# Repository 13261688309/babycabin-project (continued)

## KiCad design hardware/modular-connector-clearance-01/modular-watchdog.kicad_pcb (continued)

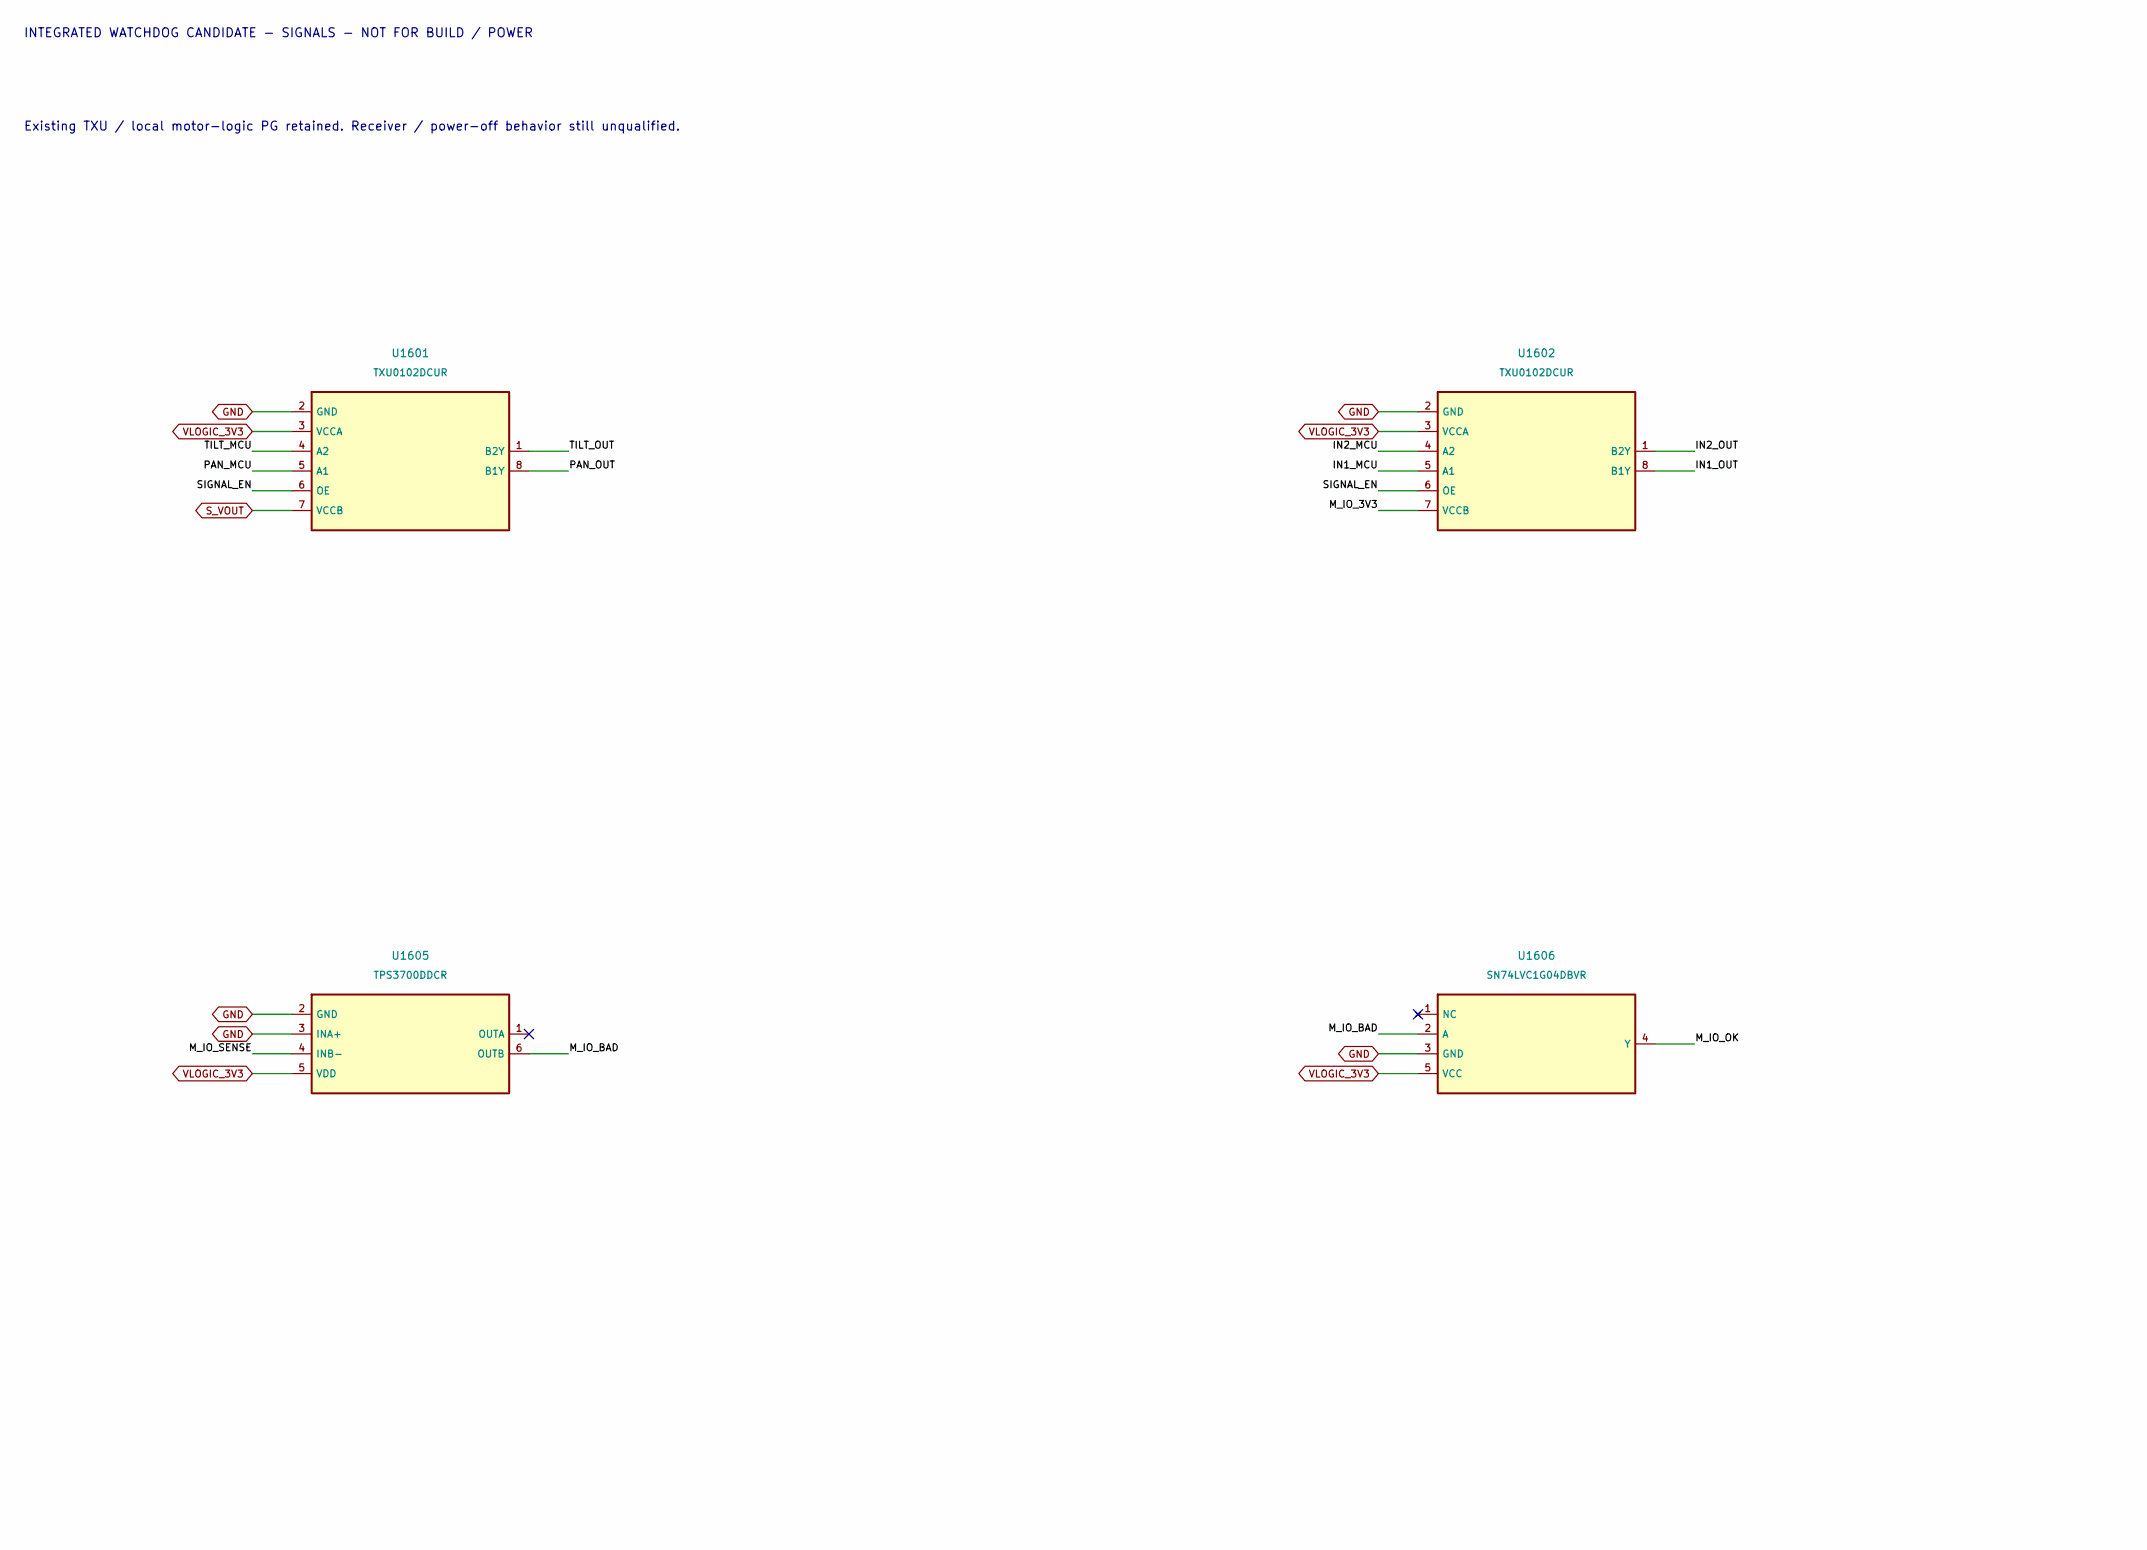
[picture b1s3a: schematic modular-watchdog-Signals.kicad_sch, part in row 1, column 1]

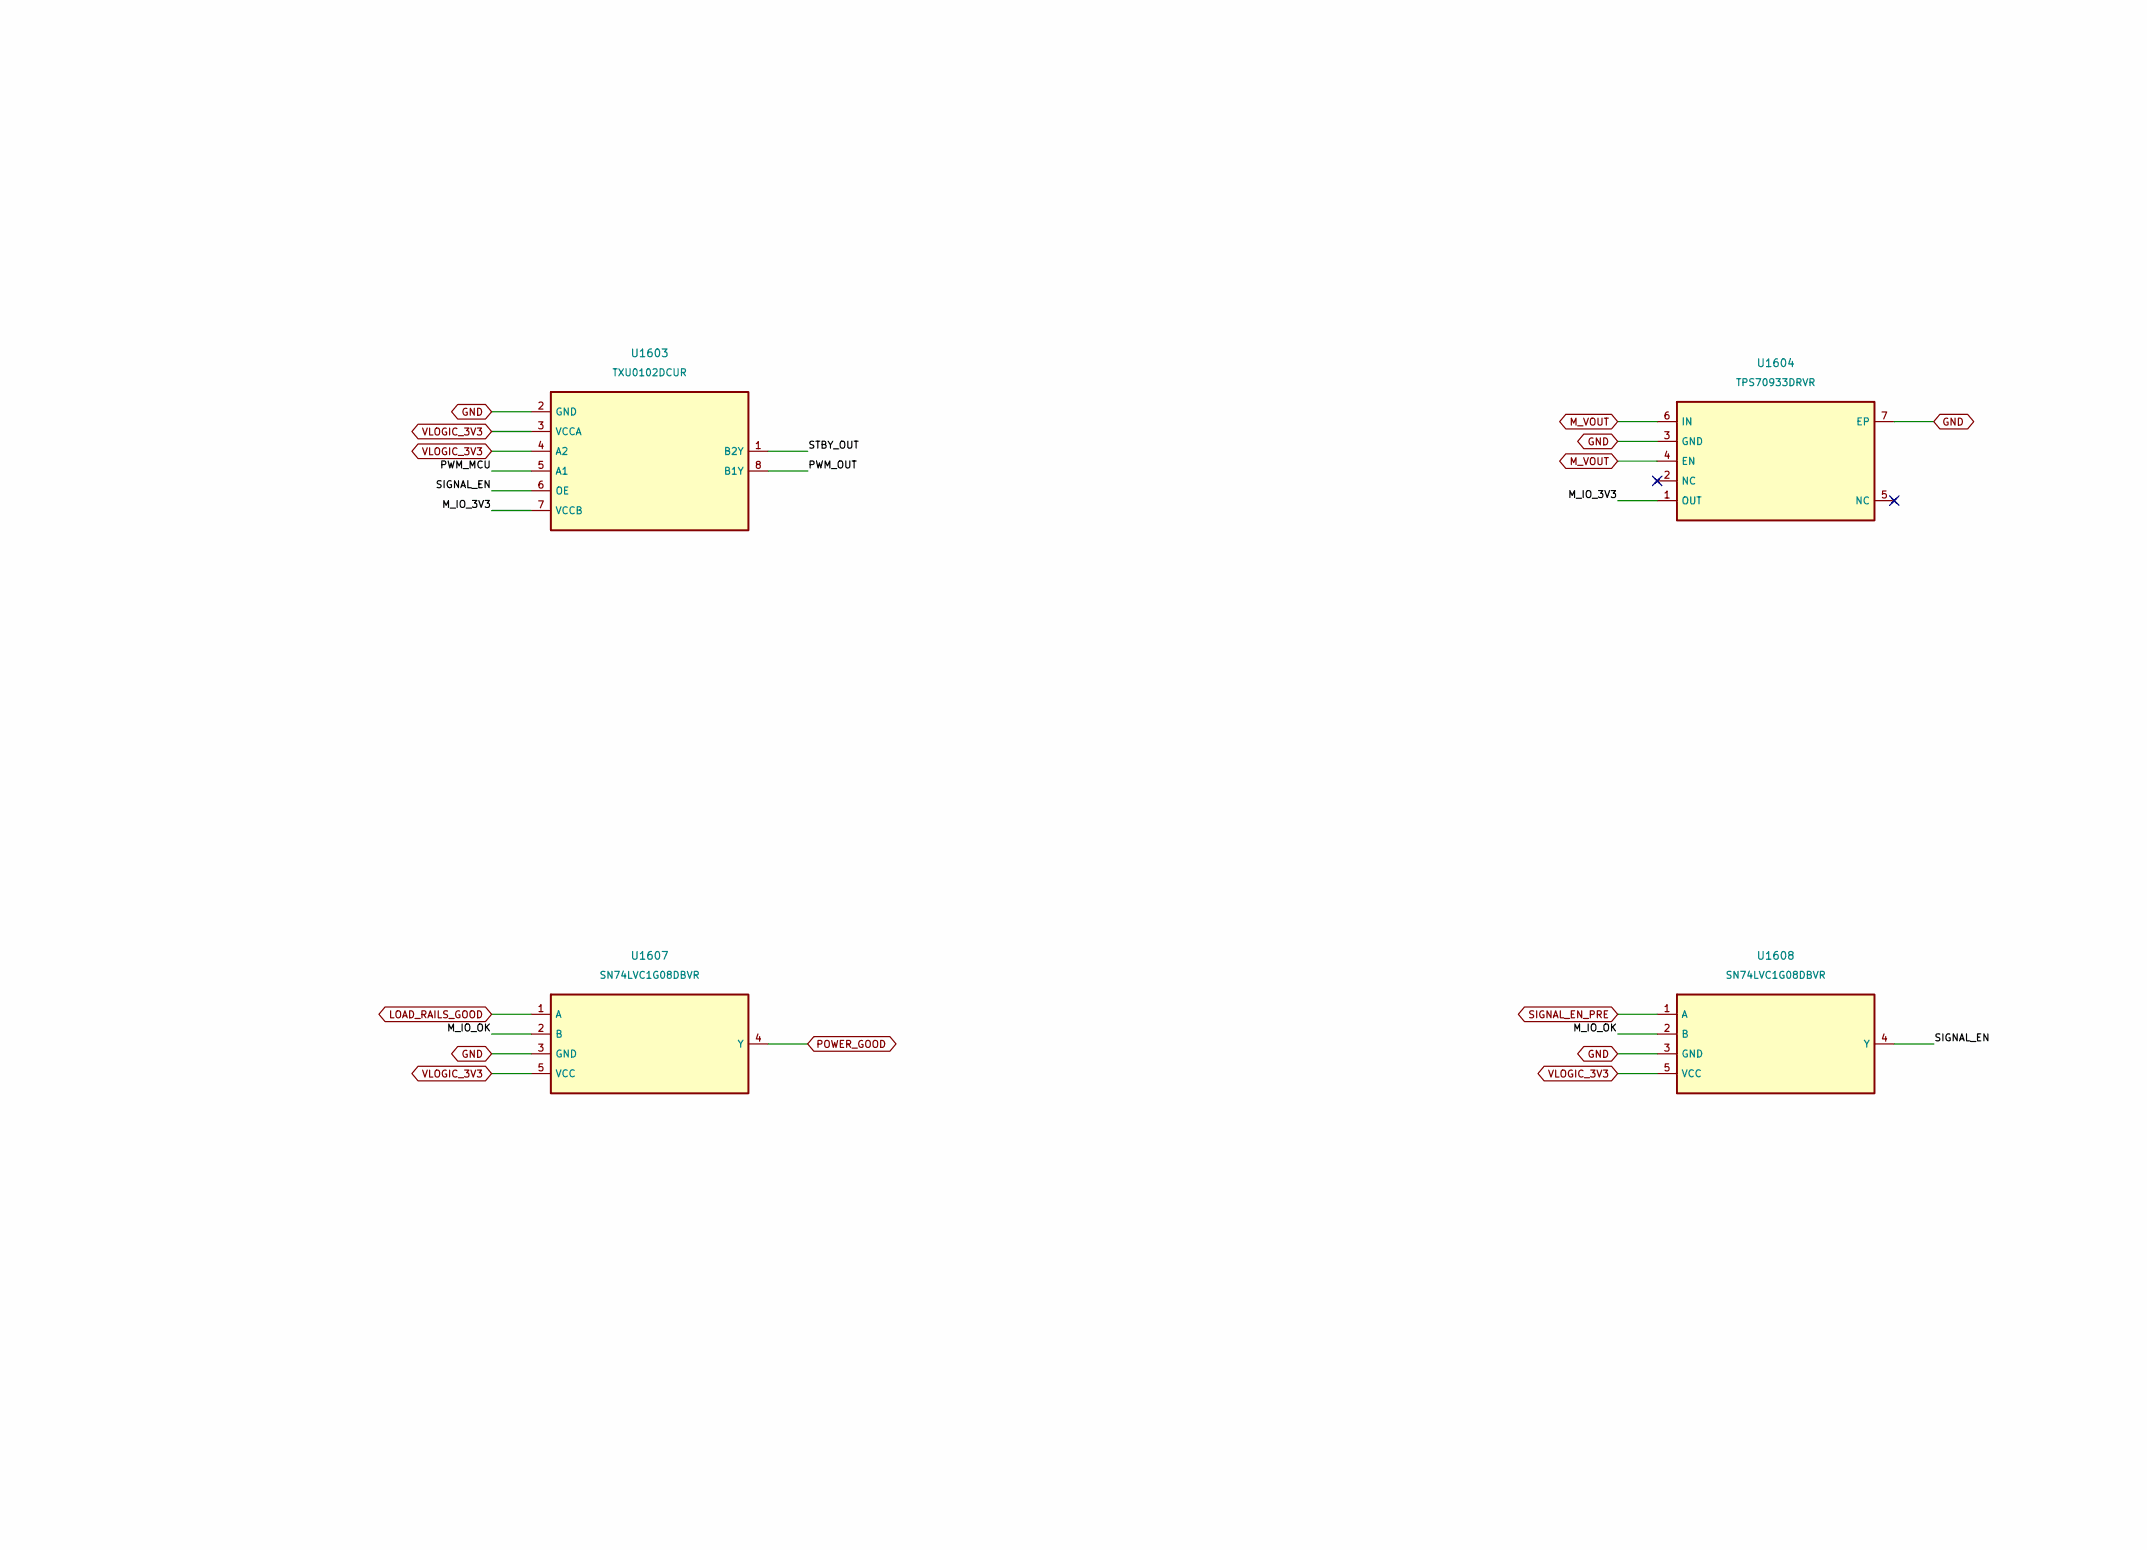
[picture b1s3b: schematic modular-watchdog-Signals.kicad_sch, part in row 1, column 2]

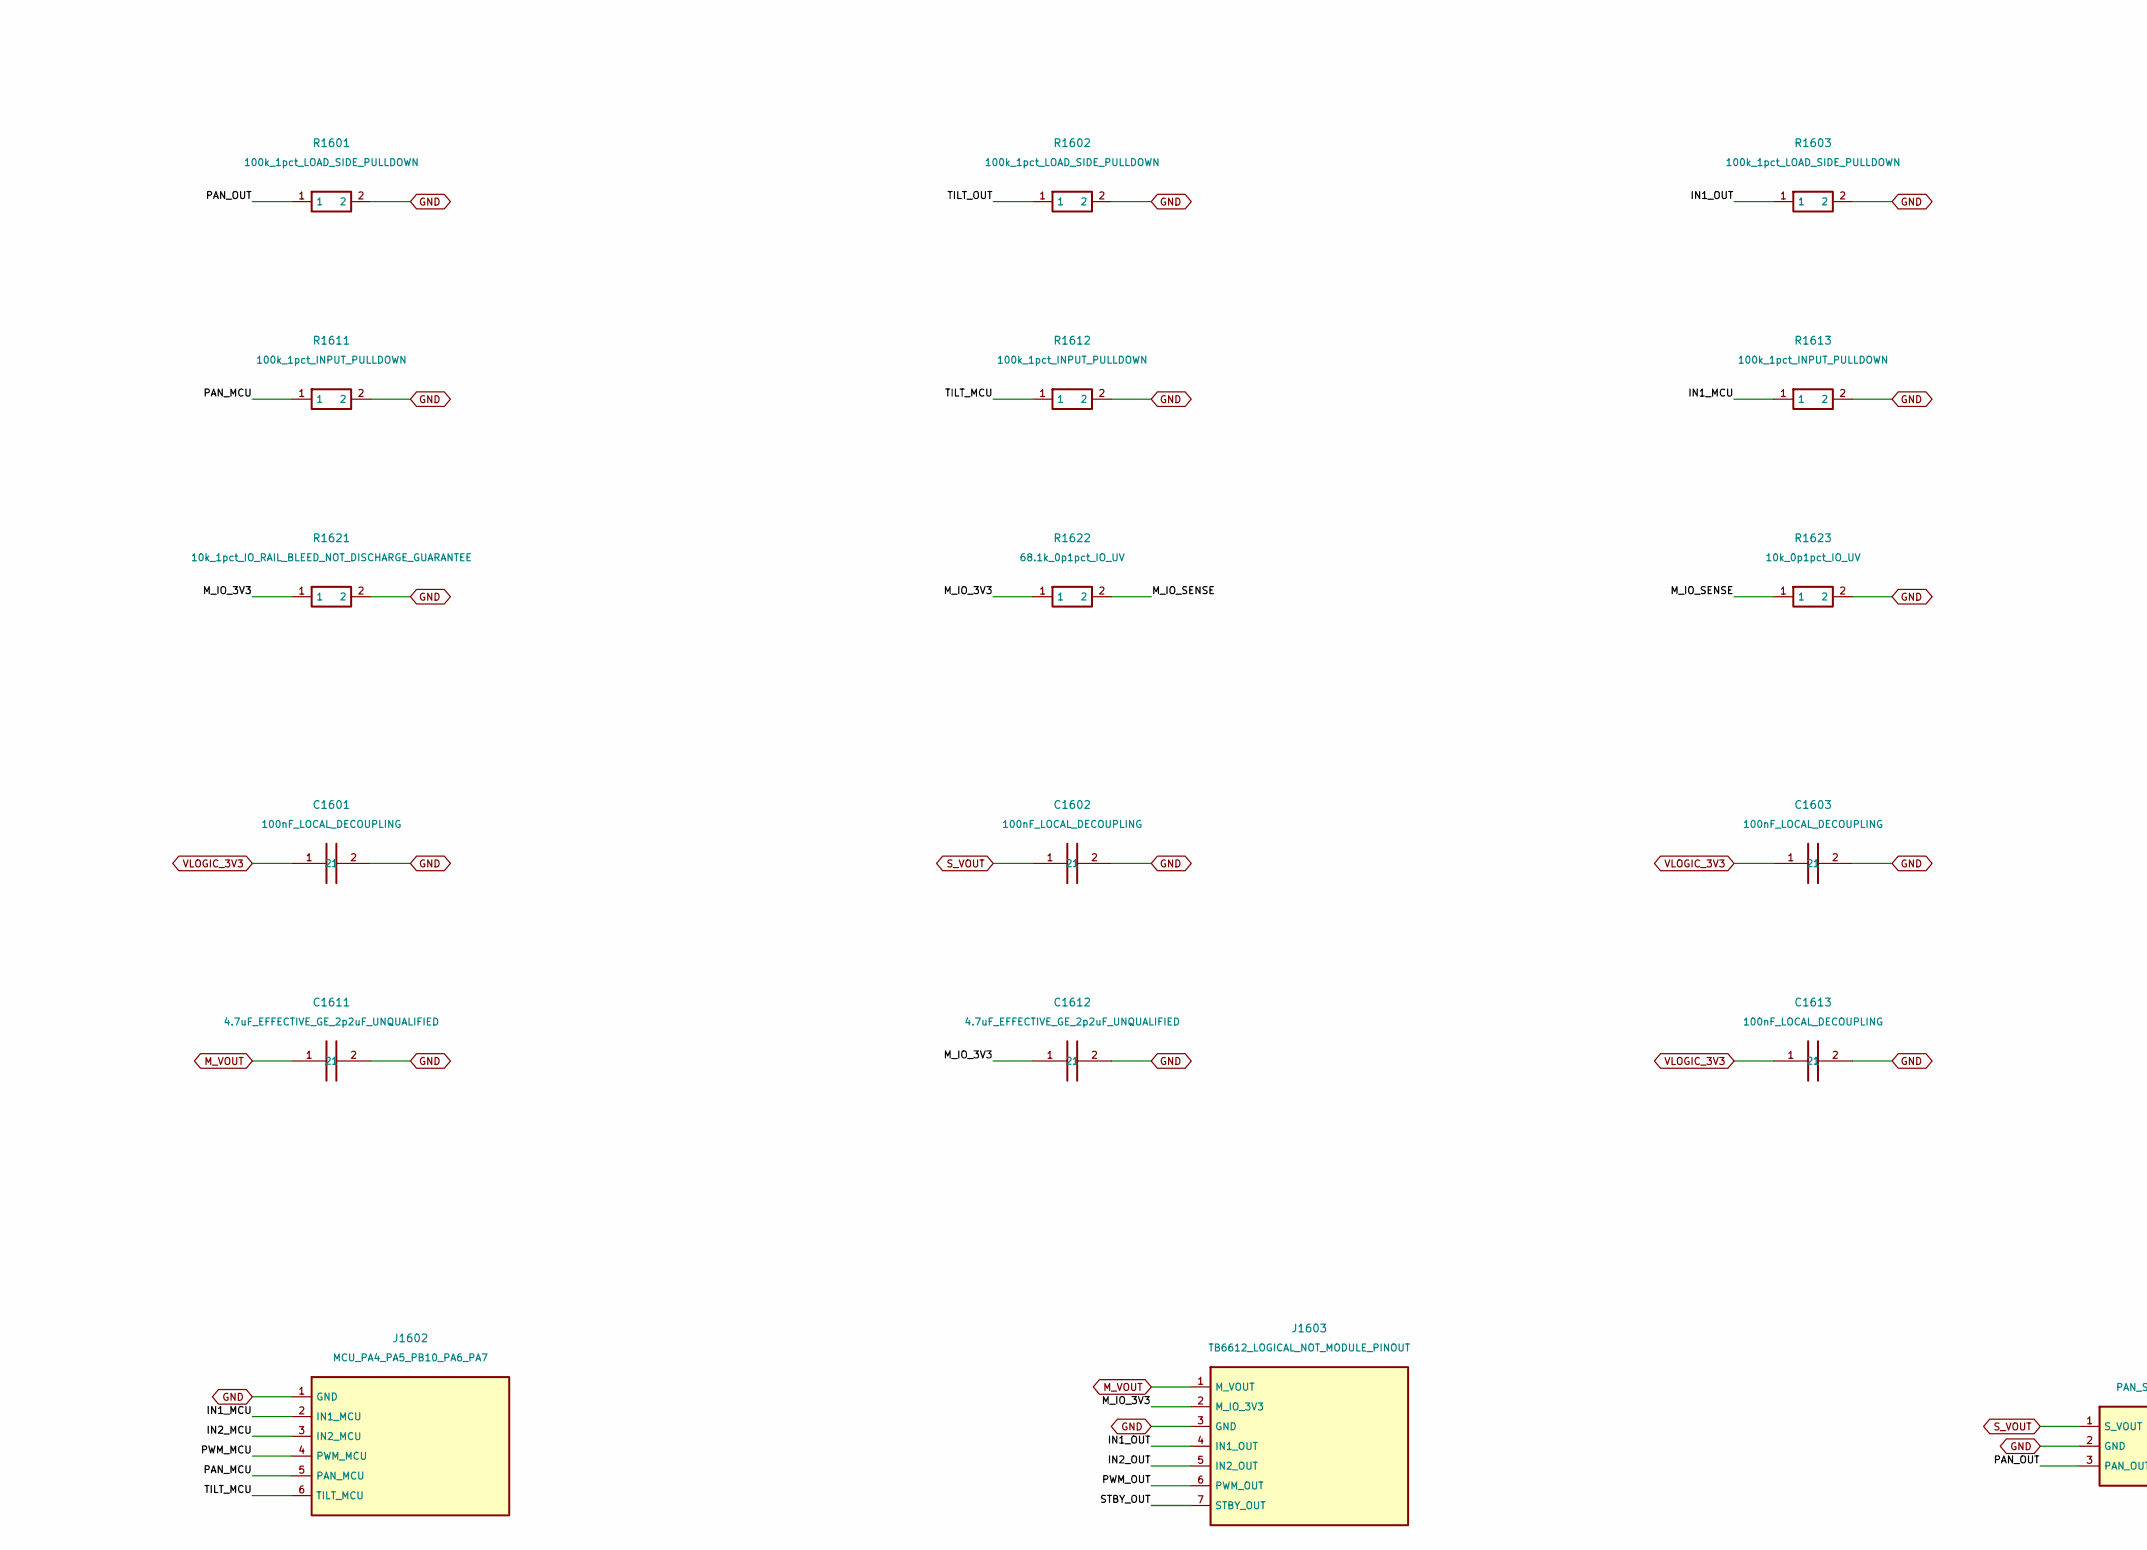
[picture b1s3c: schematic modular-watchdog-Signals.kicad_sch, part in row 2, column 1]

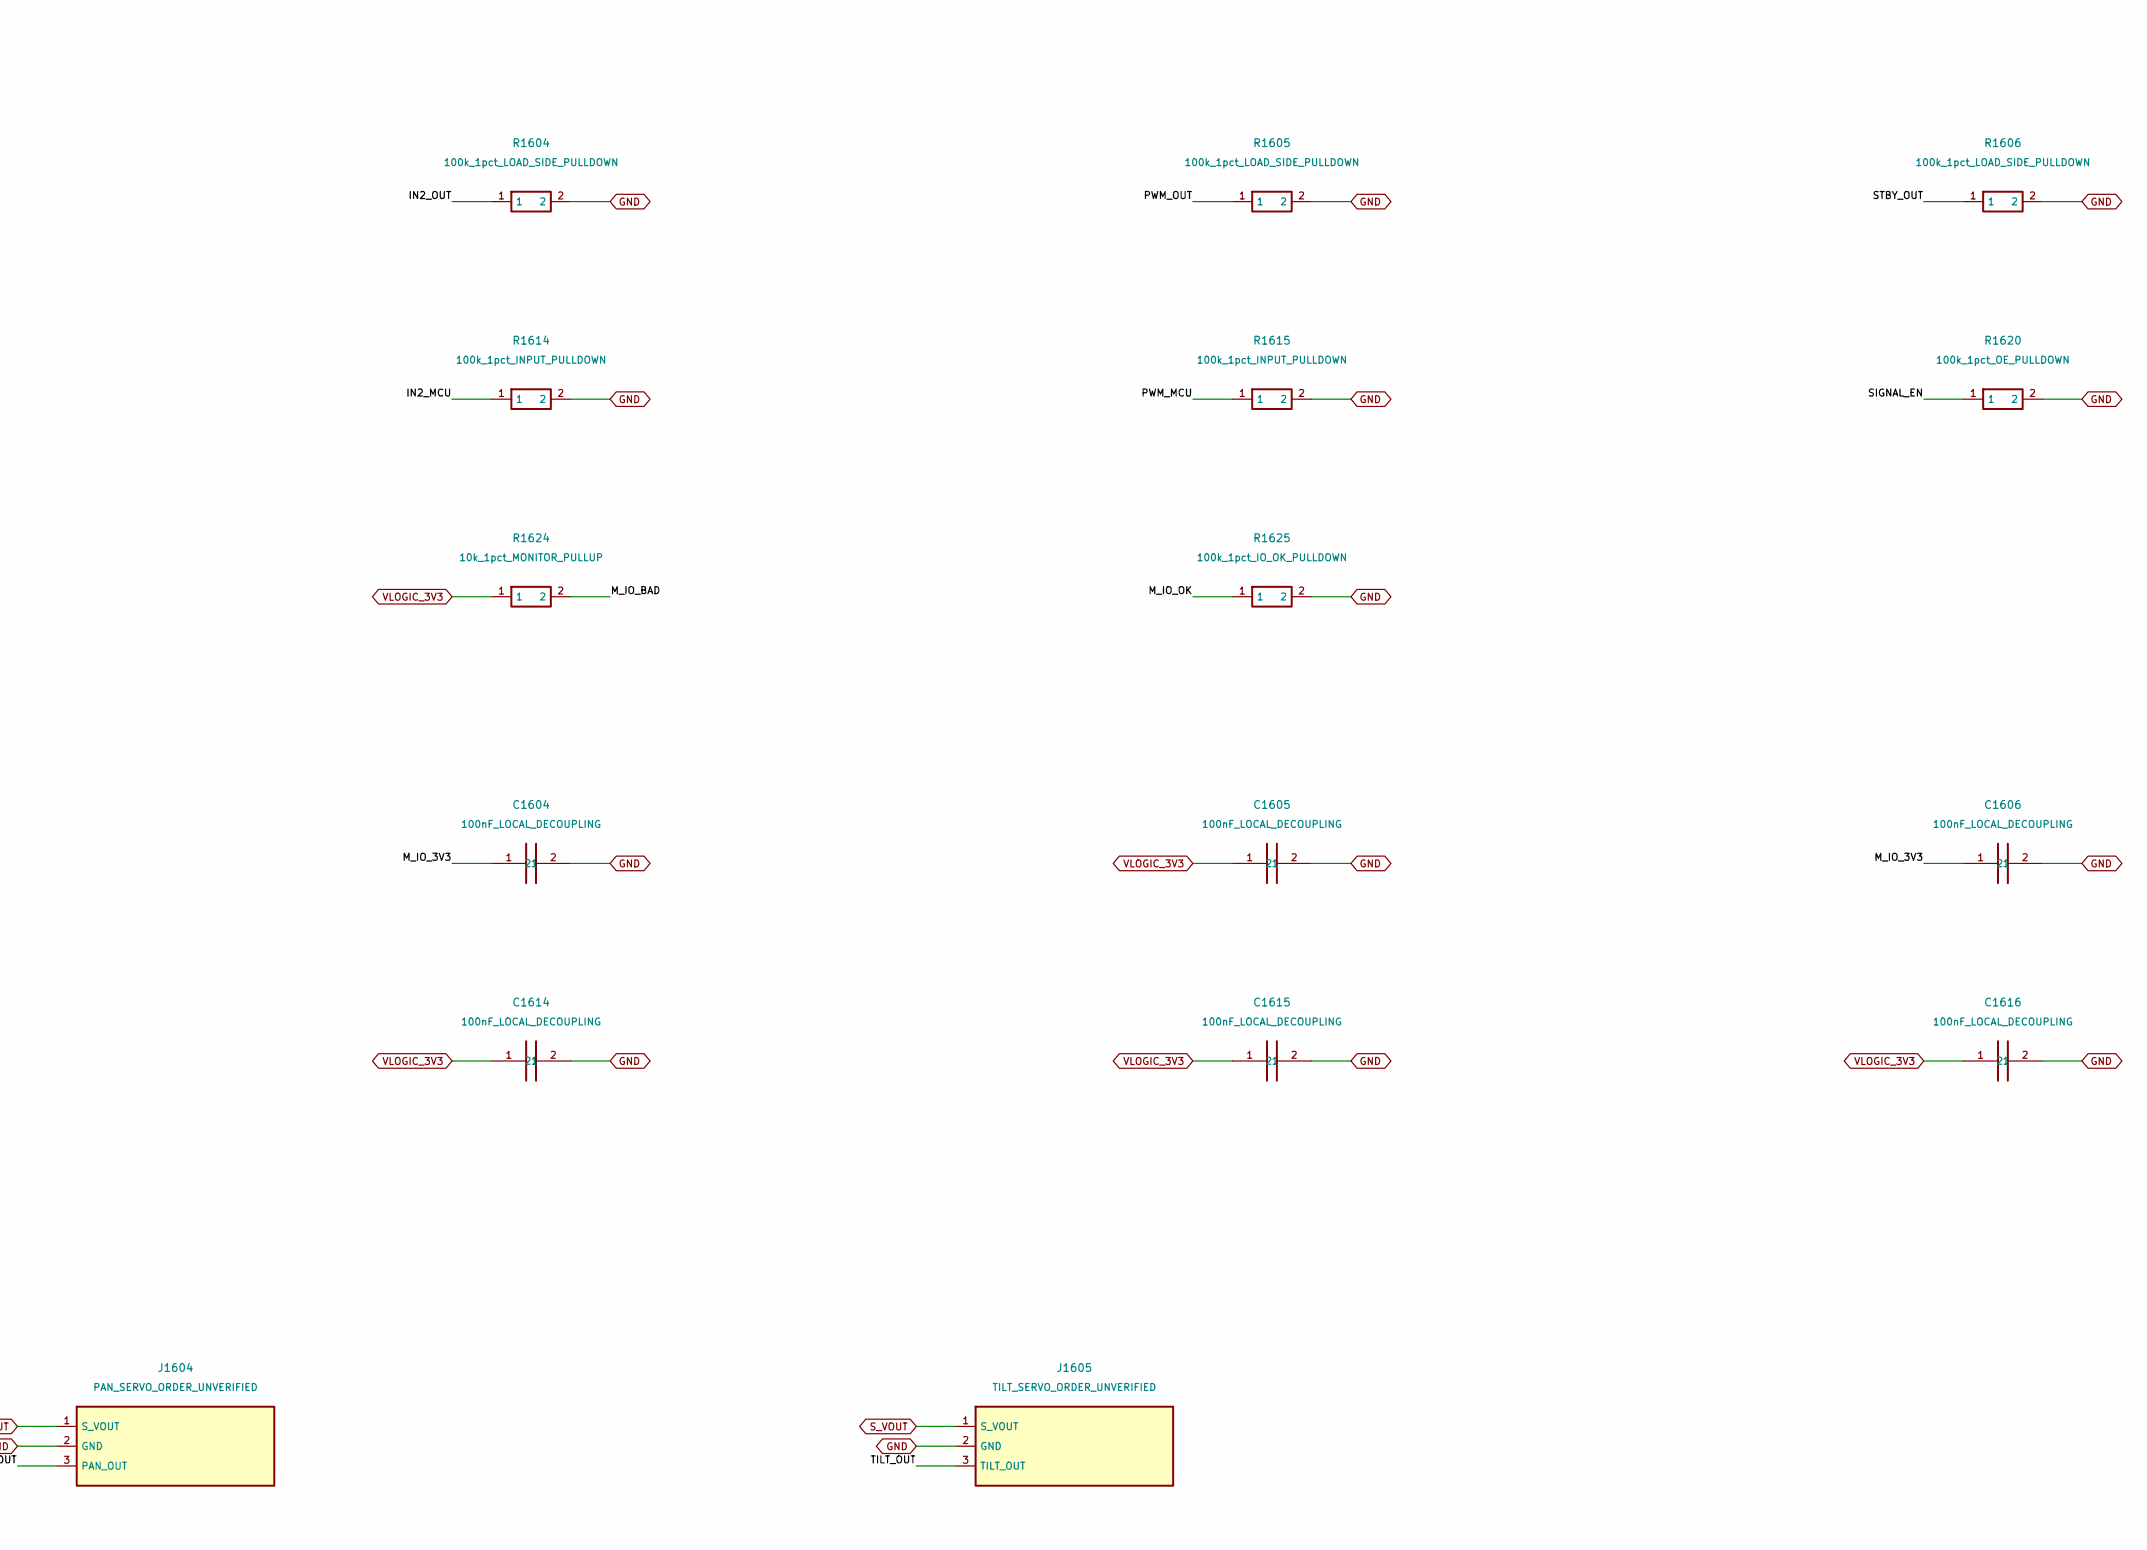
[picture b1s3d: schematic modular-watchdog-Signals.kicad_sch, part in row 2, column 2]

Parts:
C1601, C1602, C1603, C1604, C1605, C1606, C1613, C1614, C1615, C1616: 100nF_LOCAL_DECOUPLING; TDK_0603_Reflow_CapacitorDraft
C1611, C1612: 4.7uF_EFFECTIVE_GE_2p2uF_UNQUALIFIED; TDK_1206_Reflow_CapacitorDraft
J1602: MCU_PA4_PA5_PB10_PA6_PA7; JST_XH_B6B-XH-A_1x06_P2.50mm_Vertical_ConnectorDraft
J1603: TB6612_LOGICAL_NOT_MODULE_PINOUT; JST_VH_B7P-VH_1x07_P3.96mm_Vertical_ConnectorDraft
J1604: PAN_SERVO_ORDER_UNVERIFIED; JST_VH_B3P-VH_1x03_P3.96mm_Vertical_ConnectorDraft
J1605: TILT_SERVO_ORDER_UNVERIFIED; JST_VH_B3P-VH_1x03_P3.96mm_Vertical_ConnectorDraft
R1601, R1602, R1603, R1604, R1605, R1606: 100k_1pct_LOAD_SIDE_PULLDOWN; Vishay_CRCW0805_Reflow_ResistorDraft
R1611, R1612, R1613, R1614, R1615: 100k_1pct_INPUT_PULLDOWN; Vishay_CRCW0805_Reflow_ResistorDraft
R1620: 100k_1pct_OE_PULLDOWN; Vishay_CRCW0805_Reflow_ResistorDraft_AssemblyMarker
R1621: 10k_1pct_IO_RAIL_BLEED_NOT_DISCHARGE_GUARANTEE; Vishay_CRCW0805_Reflow_ResistorDraft
R1622: 68.1k_0p1pct_IO_UV; Vishay_TNPW0805_Reflow_ResistorDraft_AssemblyMarker
R1623: 10k_0p1pct_IO_UV; Vishay_TNPW0805_Reflow_ResistorDraft_AssemblyMarker
R1624: 10k_1pct_MONITOR_PULLUP; Vishay_CRCW0805_Reflow_ResistorDraft
R1625: 100k_1pct_IO_OK_PULLDOWN; Vishay_CRCW0805_Reflow_ResistorDraft
U1601, U1602, U1603: TXU0102DCUR; TI_DCU0008A_ModularLogicDraft
U1604: TPS70933DRVR; TI_DRV0006A_TPS709_SplitPaste_ThermalDraft
U1605: TPS3700DDCR; TI_DDC0006A_ModularLogicDraft
U1606: SN74LVC1G04DBVR; TI_DBV0005A_ModularLogicDraft
U1607, U1608: SN74LVC1G08DBVR; TI_DBV0005A_ModularLogicDraft

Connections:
/Signals/IN1_MCU: J1602.2 (IN1_MCU), R1613.1, U1602.5 (A1)
/Signals/IN1_OUT: J1603.4 (IN1_OUT), R1603.1, U1602.8 (B1Y)
/Signals/IN2_MCU: J1602.3 (IN2_MCU), R1614.1, U1602.4 (A2)
/Signals/IN2_OUT: J1603.5 (IN2_OUT), R1604.1, U1602.1 (B2Y)
/Signals/M_IO_3V3: C1604.1, C1606.1, C1612.1, J1603.2 (M_IO_3V3), R1621.1, R1622.1, U1602.7 (VCCB), U1603.7 (VCCB), U1604.1 (OUT)
/Signals/M_IO_BAD: R1624.2, U1605.6 (OUTB), U1606.2 (A)
/Signals/M_IO_OK: R1625.1, U1606.4 (Y), U1607.2 (B), U1608.2 (B)
/Signals/M_IO_SENSE: R1622.2, R1623.1, U1605.4 (INB-)
/Signals/PAN_MCU: J1602.5 (PAN_MCU), R1611.1, U1601.5 (A1)
/Signals/PAN_OUT: J1604.3 (PAN_OUT), R1601.1, U1601.8 (B1Y)
/Signals/PWM_MCU: J1602.4 (PWM_MCU), R1615.1, U1603.5 (A1)
/Signals/PWM_OUT: J1603.6 (PWM_OUT), R1605.1, U1603.8 (B1Y)
/Signals/SIGNAL_EN: R1620.1, U1601.6 (OE), U1602.6 (OE), U1603.6 (OE), U1608.4 (Y)
/Signals/STBY_OUT: J1603.7 (STBY_OUT), R1606.1, U1603.1 (B2Y)
/Signals/TILT_MCU: J1602.6 (TILT_MCU), R1612.1, U1601.4 (A2)
/Signals/TILT_OUT: J1605.3 (TILT_OUT), R1602.1, U1601.1 (B2Y)
GND: C1601.2, C1602.2, C1603.2, C1604.2, C1605.2, C1606.2, C1611.2, C1612.2, C1613.2, C1614.2, C1615.2, C1616.2, J1602.1 (GND), J1603.3 (GND), J1604.2 (GND), J1605.2 (GND), R1601.2, R1602.2, R1603.2, R1604.2, R1605.2, R1606.2, R1611.2, R1612.2, R1613.2, R1614.2, R1615.2, R1620.2, R1621.2, R1623.2, R1625.2, U1601.2 (GND), U1602.2 (GND), U1603.2 (GND), U1604.3 (GND), U1604.7 (EP), U1605.2 (GND), U1605.3 (INA+), U1606.3 (GND), U1607.3 (GND), U1608.3 (GND); also elsewhere on the board
LOAD_RAILS_GOOD: U1607.1 (A); also elsewhere on the board
M_VOUT: C1611.1, J1603.1 (M_VOUT), U1604.4 (EN), U1604.6 (IN); also elsewhere on the board
POWER_GOOD: U1607.4 (Y); also elsewhere on the board
SIGNAL_EN_PRE: U1608.1 (A); also elsewhere on the board
S_VOUT: C1602.1, J1604.1 (S_VOUT), J1605.1 (S_VOUT), U1601.7 (VCCB); also elsewhere on the board
VLOGIC_3V3: C1601.1, C1603.1, C1605.1, C1613.1, C1614.1, C1615.1, C1616.1, R1624.1, U1601.3 (VCCA), U1602.3 (VCCA), U1603.3 (VCCA), U1603.4 (A2), U1605.5 (VDD), U1606.5 (VCC), U1607.5 (VCC), U1608.5 (VCC); also elsewhere on the board

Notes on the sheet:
INTEGRATED WATCHDOG CANDIDATE - SIGNALS - NOT FOR BUILD / POWER
Existing TXU / local motor-logic PG retained. Receiver / power-off behavior still unqualified.
